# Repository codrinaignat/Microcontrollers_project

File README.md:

# Microcontrollers_project
I created this project back in college for a discipline called "Microcontrollers". The requirements for this project were:
- create the PCB for a project that contains a microcontroller;
- use at least a digital input, an analogic input, a digital output, a digital PWM output, a communication protocol;
- simulation in Proteus, code creation in MPLABX IDE.

The structure of the project is the following:
- the folder "Documente" contains a file in romanian with the project's requirements and 3 datasheets in english, regarding the LCD;
- the folder "MPLAB" contains the code for the chosen microcontroller (dsPIC33FJ32MC202);
- the folder "PCB" contains the schematic of the project and the printed circuit board;
- the folder "Proteus" contains the project schematic created in Isis module of Proteus. Here you can easily upload the .hex file from the "MPLAB" folder and simulate the microcontroller's functionality.

The project's functionality:

The microcontroller measures an analogic value from a temperature sensor (LM35), then displays the temperature on an Liquid Crystal Display. There are also 3 buttons: one to show the max value of the temperature, one to show the min value of the temperature and one to reset these values. The mentioned values are recorded since the system is turned on. Also, if the temperature is >23 degrees Celsius, a fan starts (DC motor)

Used components:
- LM temperature sensor;
- dsPIC33FJ32MC202 microcontroller from Microchip;
- LM016 Liquid Crystal Display;
- push buttons;
- DC motor;
- 2N2222 transistor.

The file "Proiect la disciplina Microcontrollere.docx" explains the project's functionality and contains images of the schematic, PCB and the used code. The disadvantage is that the documentation is in Romanian.

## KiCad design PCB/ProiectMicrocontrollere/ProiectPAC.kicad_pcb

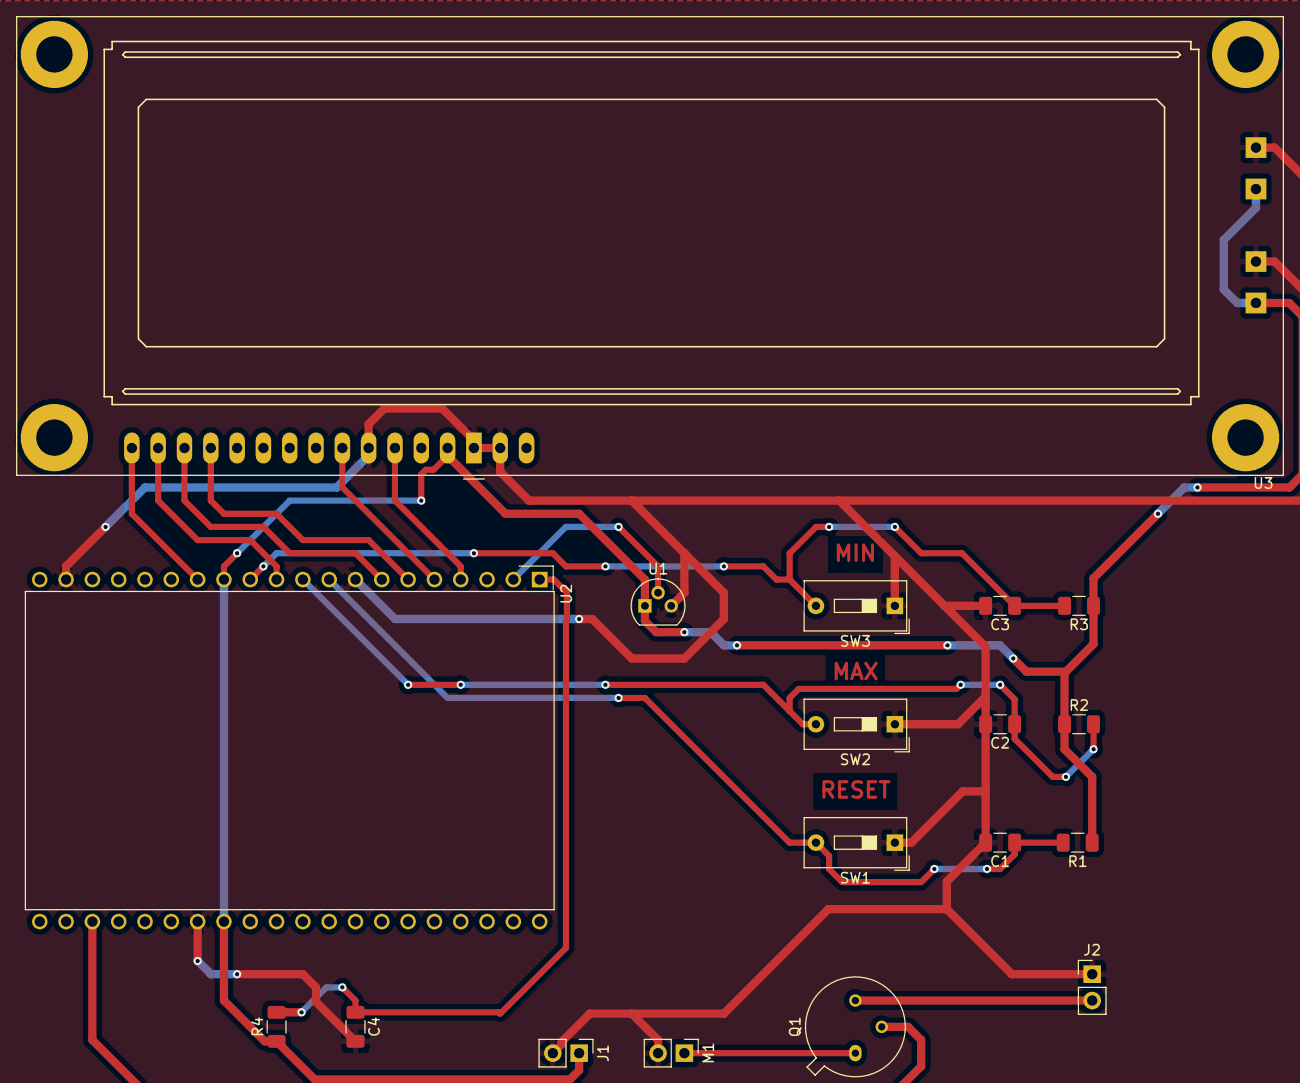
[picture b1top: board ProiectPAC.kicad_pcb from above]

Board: 2 copper layers, 18 parts (0 on the bottom side), 16 nets.

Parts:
C1, C2, C3: 1nF; C_1206_3216Metric
C4: 0.1uF; C_1206_3216Metric
J1, J2: Conn_01x02_Male; PinHeader_1x02_P2.54mm_Vertical
M1: Motor_DC; PinHeader_1x02_P2.54mm_Vertical
Q1: 2N2219; TO-39-3
R1, R2, R3: 1k; R_1206_3216Metric
R4: 10k; R_1206_3216Metric
SW1, SW2, SW3: SW_DPST_x2; SW_DIP_SPSTx01_Slide_9.78x4.72mm_W7.62mm_P2.54mm
U1: LM35-LP; TO-92
U2: DSPIC33FJ32MC202-E_SO; DE113-XX-XX
U3: LCD-016N002L

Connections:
+5V: J1.1, R1.1, R2.1, R3.1, R4.1, U1.1, U2.13, U2.28, U3.2, U3.A1, U3.A2
+12V: J2.2, Q1.3
GND: C1.2, C2.2, C3.2, C4.2, J1.2, J2.1, M1.2, SW1.1, SW2.1, SW3.1, U1.3, U2.8, U2.19, U2.27, U3.1, U3.5, U3.15, U3.K1, U3.K2
unnamed: C1.1, R1.2, SW1.2, U2.9
unnamed: C2.1, R2.2, SW2.2, U2.10
unnamed: C3.1, R3.2, SW3.2, U2.12
unnamed: C4.1, R4.2, U2.1
unnamed: M1.1, Q1.1
unnamed: Q1.2, U2.23
unnamed: U1.2, U2.2
unnamed: U2.4, U3.4
unnamed: U2.5, U3.6
unnamed: U2.6, U3.11
unnamed: U2.7, U3.12
unnamed: U2.11, U3.13
unnamed: U2.14, U3.14

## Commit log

2023-07-23 no message
2023-08-25 Update README.md
    - Added the structure of the project, the project's functionality and used components.
